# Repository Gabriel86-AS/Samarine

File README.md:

# Samarine
 
Samarine is a remotely operated underwater vehicle (ROV), meant to make underwater robotics more accessible to students and researchers who want to leverage its advantages to increase our understanding of marine environments.
 
It is made with a 3D printed chassis and 2 custom PCB boards (files on this repo), and an IP camera plus 2 LEDs. It features an ESP32 as the main "brain" of the robot. The ESP32 will receive control signals from a laptop and the camera will stream video to the laptop directly in H.264 video. 
 
## Why do this project?
Well, I live in a city where marine biology is very diverse and people from all over the country come to study it. But for local students, this kind of research is not always accessible, since you would need to acquire expensive diving equipment and courses in order to be able to explore the marine environment. Samarine is a way to make research more accessible. V1 includes just a camera, but it also leaves many ESP32 pins free to use for module attachment. Being completely open source, people can make their own modules and perform different kinds of research for a fraction of the cost of diving (sometimes even with more precision).

 ## propeler 
 you can use any. but im planning to use this https://www.printables.com/model/405235 for toroidal propelers
## Motor distribution
 
It has 3 motors: one to go up and down, and two for going forward and turning left or right.
 
## 3D assembly 
Well, I think it's pretty intuitive. There are 6 parts made to be printed in a 3D printer with an area of at least 32×33 cm. First you permanently glue with superglue the parts that make the top and bottom part.

Finally, we just screw the top and bottom parts together with M3 screws, attach the motors to the motor pieces and screw everything together.

## Quick guide on its electronics

The hull has a **12-pin waterproof connector** (M16, IP68) in the end cap. Everything that leaves the hull goes through it. The PCB's tether header J1 uses 6 of those pins; the camera's Ethernet pigtail goes straight to the connector and does not pass through the PCB.
 
**Tether connector (12 pins)**
 
| Pin | Signal | To | Notes |
| --- | --- | --- | --- |
| 1 | RS+ (A) | J1-2 | Twisted pair with pin 2 |
| 2 | RS− (B) | J1-1 | |
| 3 | CAM1 | Camera pigtail | Straight to the camera, not through the PCB. Twisted pair with pin 4 |
| 4 | CAM2 | Camera pigtail | |
| 5 | CAM3 | Camera pigtail | Twisted pair with pin 6 |
| 6 | CAM4 | Camera pigtail | |
| 7 | 1S | J1-4 | Balance tap |
| 8 | 2S | J1-5 | Battery + |
| 9 | GND | J1-6 | Battery − (BAT−) |
| 10 | ON | J1-3 | Turns the ROV on |
| 11 | Spare | — |  |
| 12 | Spare | — |  |
 
100 Mb Ethernet only uses two pairs (RJ45 pins 1, 2, 3, 6), so one cable pair stays free for RS-485. Keep each signal pair on one twisted pair of the cable.
 
**Inside the hull**
 
- **Battery → J7:** BAT−, 1S mid-tap, 2S+. Use thick wire (≥ 18 AWG) on BAT− and 2S+, since all three ESCs draw from it.
- **ESCs:** soldered to the board on their power and signal pads. Each ESC's 3 motor wires go to its thruster; swap any two to reverse spin (or flip it in BLHeliSuite).
- **Camera:** power from J2 (CAM+, GND); Ethernet pigtail to connector pins 3–6.
- **Lights:** J8.
- **Sensors / modules:** J3 (I²C) and J4–J6 (GPIO), routed to the front module connectors.
## Where electronics go
 (will do more detailed assembly tutorial with images once i got the hardware)

Note that the LED path is for both the LED star and the LED controller.

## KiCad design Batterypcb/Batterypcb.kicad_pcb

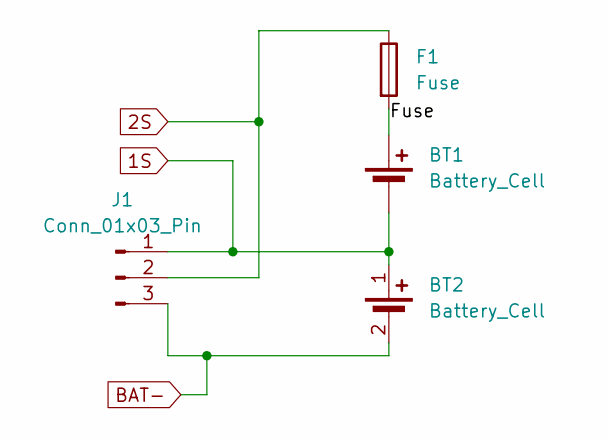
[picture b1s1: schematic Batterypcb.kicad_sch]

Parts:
BT1, BT2: Battery_Cell; BatteryHolder_18650_2x_SideBySide_Clamp_78x46mm
F1: Fuse; Fuse_MIDI_150A_Bolt_M5
J1: Conn_01x03_Pin; BatteryPads

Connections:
1S: BT1.2 (-), BT2.1 (+), J1.1
2S: F1.1, J1.2
/Fuse: BT1.1 (+), F1.2
BAT-: BT2.2 (-), J1.3

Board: 2 copper layers, 4 parts (0 on the bottom side), 4 nets, no tracks yet.
